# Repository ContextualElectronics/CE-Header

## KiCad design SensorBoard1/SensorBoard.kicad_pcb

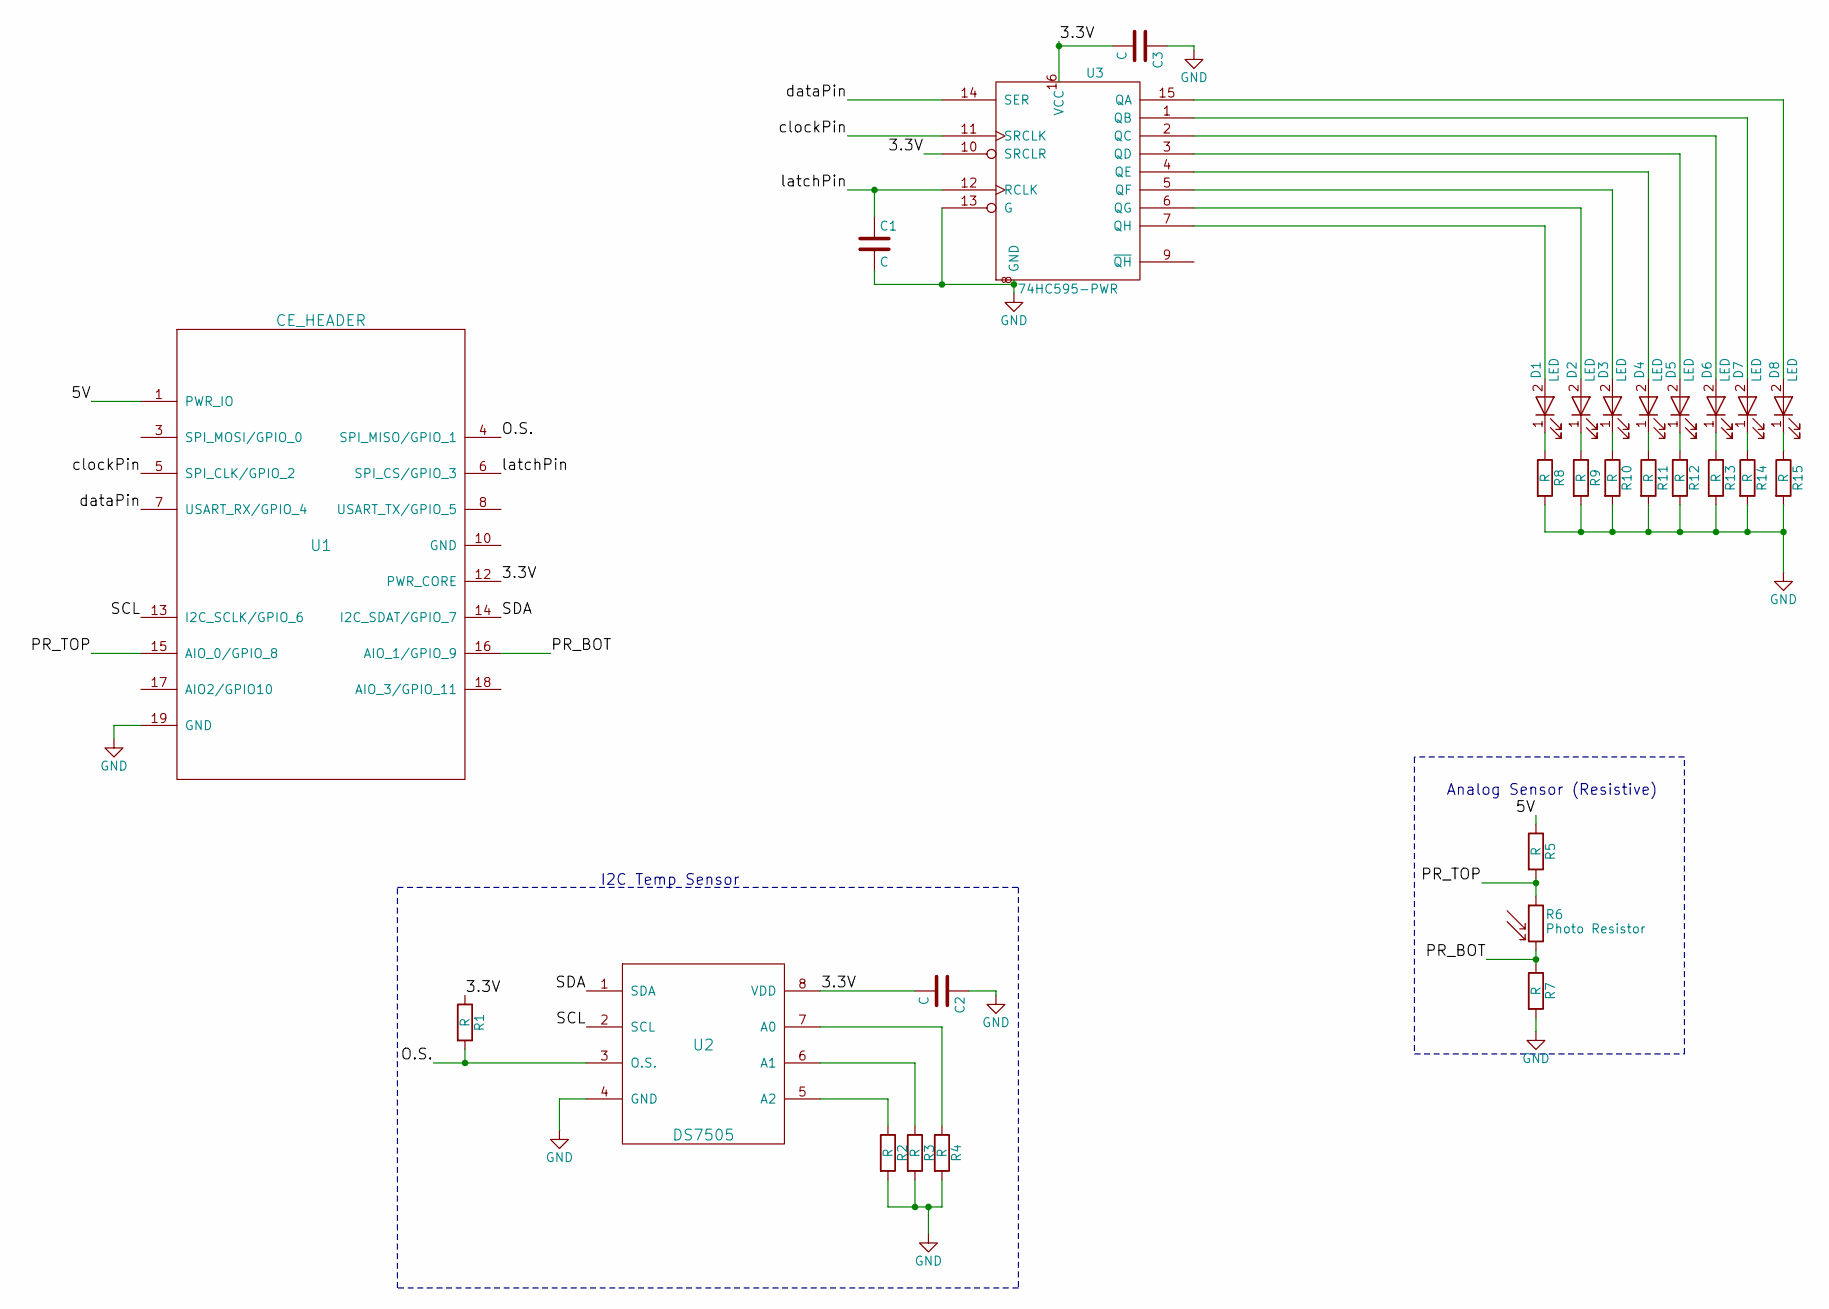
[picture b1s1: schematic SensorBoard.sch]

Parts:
C1, C2, C3: C; C_0805
D1, D2, D3, D4, D5, D6, D7, D8: LED; LED_0805
R1, R2, R3, R4, R5, R7, R8, R9, R10, R11, R12, R13, R14, R15: R; R_0805
R6: Photo Resistor; CP_Radial_Tantal_D5.5mm_P5.00mm; MPN PDV-P8103
U1: CE_HEADER; CE_Header
U2: DS7505; SOIC-8-1EP_3.9x4.9mm_Pitch1.27mm
U3: 74HC595-PWR; SOIC-16_3.9x9.9mm_Pitch1.27mm; MPN MM74HC595MX

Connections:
/3.3V: C2.2, C3.2, R1.1, U1.12 (PWR_CORE), U2.8 (VDD), U3.10 (SRCLR), U3.16 (VCC)
/5V: R5.1, U1.1 (PWR_IO)
/O.S.: R1.2, U1.4 (SPI_MISO/GPIO_1), U2.3 (O.S.)
/PR_BOT: R6.2, R7.1, U1.16 (AIO_1/GPIO_9)
/PR_TOP: R5.2, R6.1, U1.15 (AIO_0/GPIO_8)
/SCL: U1.13 (I2C_SCLK/GPIO_6), U2.2 (SCL)
/SDA: U1.14 (I2C_SDAT/GPIO_7), U2.1 (SDA)
/clockPin: U1.5 (SPI_CLK/GPIO_2), U3.11 (SRCLK)
/dataPin: U1.7 (USART_RX/GPIO_4), U3.14 (SER)
/latchPin: C1.1, U1.6 (SPI_CS/GPIO_3), U3.12 (RCLK)
GND: C1.2, C2.1, C3.1, R2.2, R3.2, R4.2, R7.2, R8.2, R9.2, R10.2, R11.2, R12.2, R13.2, R14.2, R15.2, U1.19 (GND), U2.4 (GND), U3.8 (GND), U3.13 (G)
unnamed: D1.1 (K), R8.1
unnamed: D1.2 (A), U3.7 (QH)
unnamed: D2.1 (K), R9.1
unnamed: D2.2 (A), U3.6 (QG)
unnamed: D3.1 (K), R10.1
unnamed: D3.2 (A), U3.5 (QF)
unnamed: D4.1 (K), R11.1
unnamed: D4.2 (A), U3.4 (QE)
unnamed: D5.1 (K), R12.1
unnamed: D5.2 (A), U3.3 (QD)
unnamed: D6.1 (K), R13.1
unnamed: D6.2 (A), U3.2 (QC)
unnamed: D7.1 (K), R14.1
unnamed: D7.2 (A), U3.1 (QB)
unnamed: D8.1 (K), R15.1
unnamed: D8.2 (A), U3.15 (QA)
unnamed: R2.1, U2.5 (A2)
unnamed: R3.1, U2.6 (A1)
unnamed: R4.1, U2.7 (A0)

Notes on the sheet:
Analog Sensor (Resistive)
I2C Temp Sensor

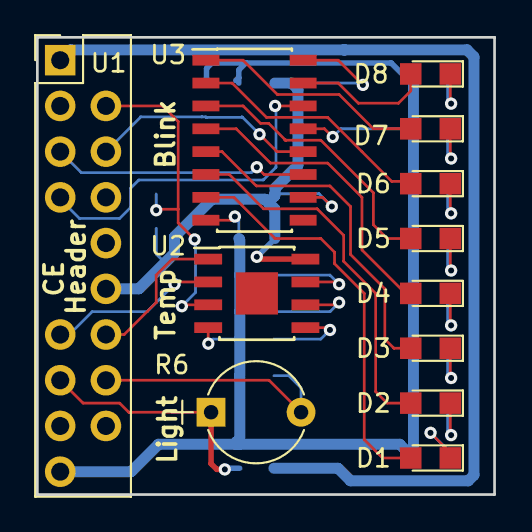
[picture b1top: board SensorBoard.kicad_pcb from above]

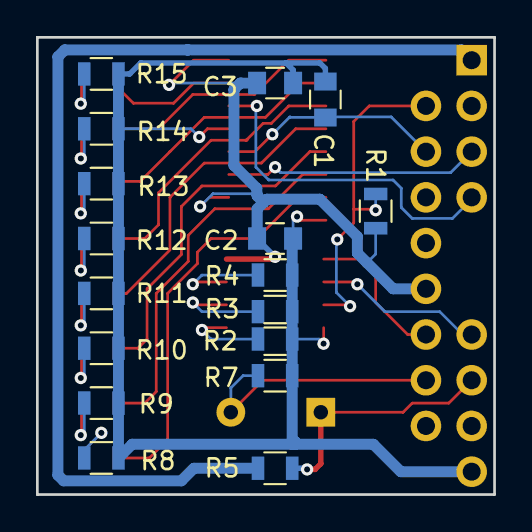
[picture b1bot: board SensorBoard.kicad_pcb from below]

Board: 2 copper layers, 25.4 x 25.4 mm, 29 parts (17 on the bottom side), 30 nets.

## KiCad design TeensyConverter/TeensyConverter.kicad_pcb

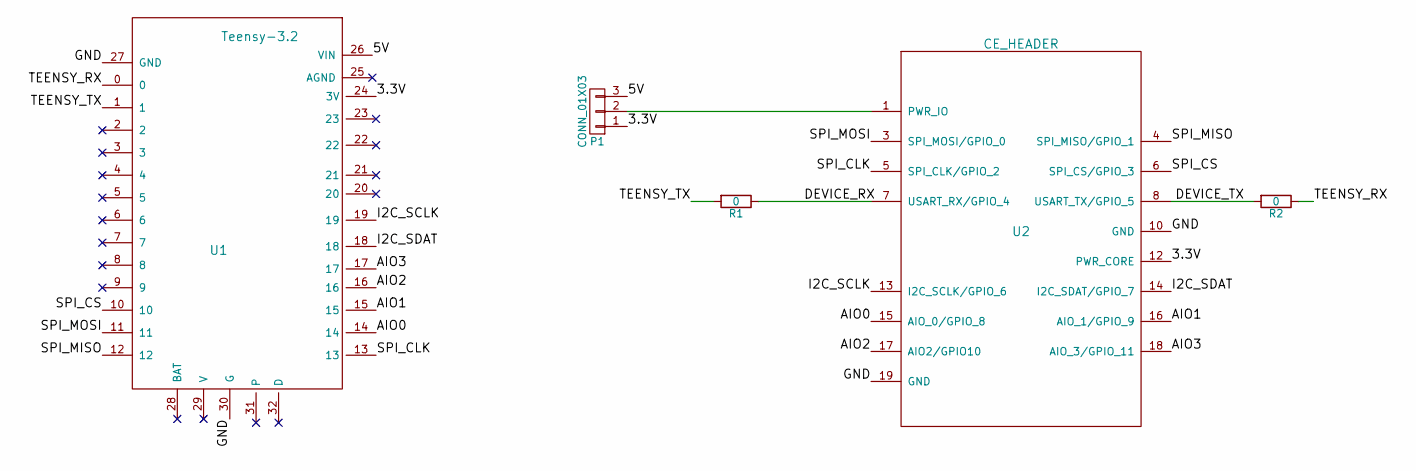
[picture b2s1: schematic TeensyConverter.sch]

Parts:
P1: CONN_01X03; Pin_Header_Straight_1x03_Pitch2.54mm
R1, R2: 0; R_0805_HandSoldering
U1: Teensy-3.2; Teensy-32
U2: CE_HEADER; CE_Header

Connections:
/3.3V: P1.1, U1.24 (3V), U2.12 (PWR_CORE)
/5V: P1.3, U1.26 (VIN)
/AIO0: U1.14, U2.15 (AIO_0/GPIO_8)
/AIO1: U1.15, U2.16 (AIO_1/GPIO_9)
/AIO2: U1.16, U2.17 (AIO2/GPIO10)
/AIO3: U1.17, U2.18 (AIO_3/GPIO_11)
/DEVICE_RX: R1.1, U2.7 (USART_RX/GPIO_4)
/DEVICE_TX: R2.2, U2.8 (USART_TX/GPIO_5)
/GND: U1.27 (GND), U1.30 (G), U2.10 (GND), U2.19 (GND)
/I2C_SCLK: U1.19, U2.13 (I2C_SCLK/GPIO_6)
/I2C_SDAT: U1.18, U2.14 (I2C_SDAT/GPIO_7)
/SPI_CLK: U1.13, U2.5 (SPI_CLK/GPIO_2)
/SPI_CS: U1.10, U2.6 (SPI_CS/GPIO_3)
/SPI_MISO: U1.12, U2.4 (SPI_MISO/GPIO_1)
/SPI_MOSI: U1.11, U2.3 (SPI_MOSI/GPIO_0)
/TEENSY_RX: R2.1, U1.0
/TEENSY_TX: R1.2, U1.1
unnamed: P1.2, U2.1 (PWR_IO)

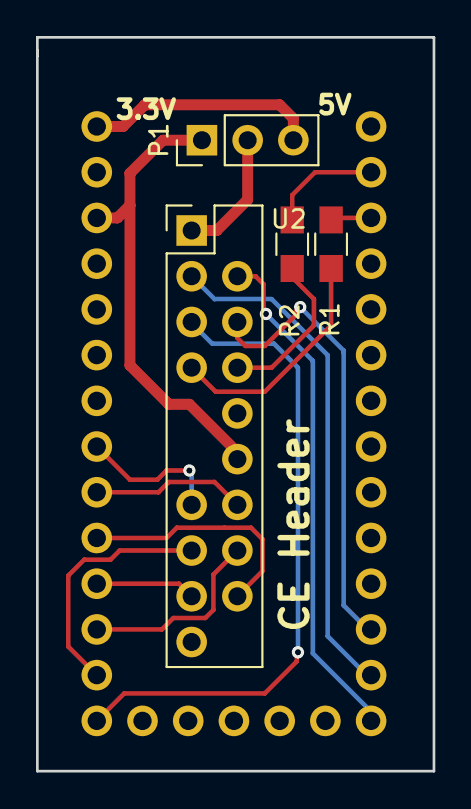
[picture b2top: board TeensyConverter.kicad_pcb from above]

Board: 2 copper layers, 22.0 x 40.8 mm, 5 parts (1 on the bottom side), 18 nets.

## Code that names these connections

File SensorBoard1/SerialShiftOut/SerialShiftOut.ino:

#define CE_spi_cs_gpio3 10
#define CE_spi_mosi_gpio0 11
#define CE_spi_miso_gpio1 12
#define CE_spi_clk_gpio2 13
#define CE_usart_rx_gpio4 1
#define CE_usart_tx_gpio5 0
#define CE_i2c_sclk_gpio6 19
#define CE_i2c_sdat_gpio7 18
#define CE_aio0_gpio8 14
#define CE_aio1_gpio9 15
#define CE_aio2_gpio10 16
#define CE_aio3_gpio11 17

/*
  Shift Register Example
 for 74HC595 shift register

 This sketch turns reads serial input and uses it to set the pins
 of a 74HC595 shift register.

 Hardware:
 * 74HC595 shift register attached to pins 8, 12, and 11 of the Arduino,
 as detailed below.
 * LEDs attached to each of the outputs of the shift register.


 Created 22 May 2009
 Created 23 Mar 2010
 by Tom Igoe

 */

//Pin connected to latch pin (ST_CP) of 74HC595
const int latchPin = CE_spi_cs_gpio3;
//Pin connected to clock pin (SH_CP) of 74HC595
const int clockPin = CE_spi_clk_gpio2;
////Pin connected to Data in (DS) of 74HC595
const int dataPin = CE_usart_rx_gpio4;

void setup() {
  //set pins to output because they are addressed in the main loop
  pinMode(latchPin, OUTPUT);
  pinMode(dataPin, OUTPUT);  
  pinMode(clockPin, OUTPUT);
  Serial.begin(9600);
  Serial.println("reset");
}

void loop() {
  if (Serial.available() > 0) {
    // ASCII '0' through '9' characters are
    // represented by the values 48 through 57.
    // so if the user types a number from 0 through 9 in ASCII, 
    // you can subtract 48 to get the actual value:
    int bitToSet = Serial.read() - 48;

  // write to the shift register with the correct bit set high:
    registerWrite(bitToSet, HIGH);
  }
}

// This method sends bits to the shift register:

void registerWrite(int whichPin, int whichState) {
// the bits you want to send
  byte bitsToSend = 0;

  // turn off the output so the pins don't light up
  // while you're shifting bits:
  digitalWrite(latchPin, LOW);

  // turn on the next highest bit in bitsToSend:
  bitWrite(bitsToSend, whichPin, whichState);

  // shift the bits out:
  shiftOut(dataPin, clockPin, MSBFIRST, 0b00101100); 

    // turn on the output so the LEDs can light up:
  digitalWrite(latchPin, HIGH);

}

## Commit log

2017-02-16 Removed original pin header
2017-02-17 Added new directory for example project
2017-02-17 Moved all original CE header files to separate directory
2017-02-17 Connected teensy header to ce header
2017-02-20 Associated components and added to layout
2017-02-20 1st pass at layout
2017-02-20 Swapped CE header 180 degrees
2017-02-21 Finished layout of CE header converter for Teensy with flipped footprints
2017-02-22 Started another subdirectory for a sensor board
2017-02-22 Updated board for ground connection
2017-02-23 Created symbol for DS7505 temp sensor
2017-03-01 Finished schematic for small sensor board
2017-03-05 Associated footprints
2017-03-05 Finished 1.0 Layout
2017-10-25 Created translation layer for CE header in Arduino
2017-10-25 Serial test program with correct pin 13
2017-10-27 Small test program for he LDR analog input
